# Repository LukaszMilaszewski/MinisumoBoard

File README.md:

# MinisumoBoard
electric board for minisumo robot designed in KiCad

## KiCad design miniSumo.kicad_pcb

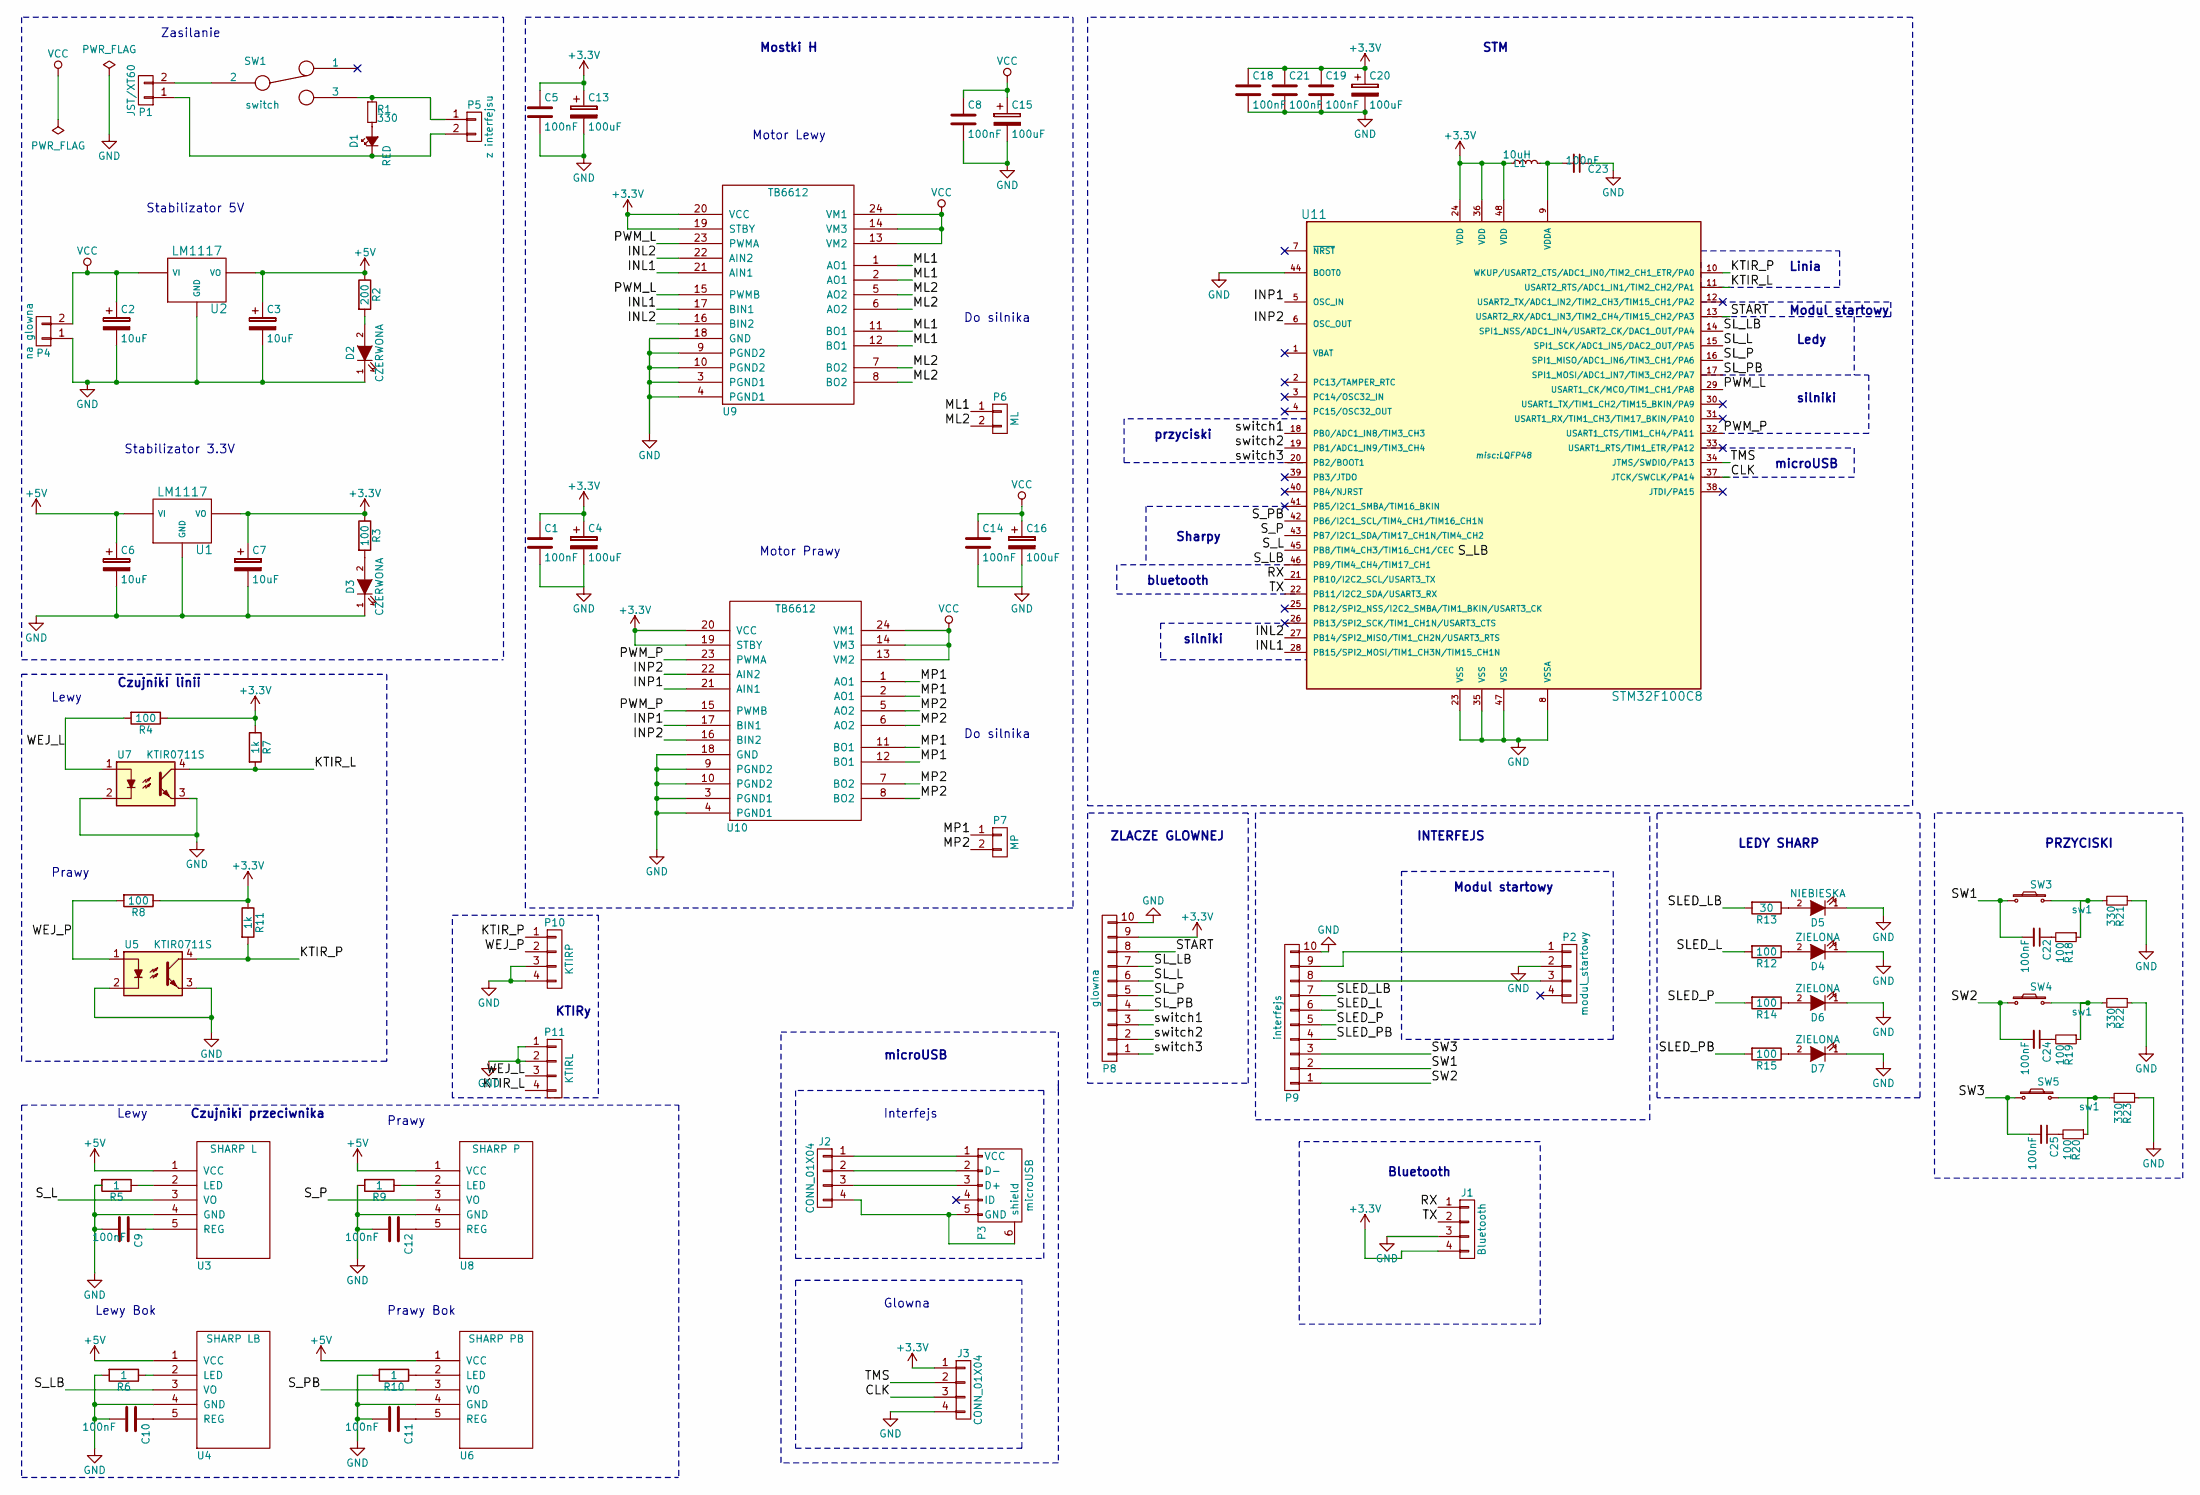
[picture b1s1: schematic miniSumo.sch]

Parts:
C1, C5, C8, C9, C10, C11, C12, C14, C18, C19, C21, C22, C23, C24, C25: 100nF; C_0805_HandSoldering
C2, C3, C6, C7: 10uF; CP_Tantalum_Case-B_EIA-3528-21_Hand
C4, C13, C15, C16, C20: 100uF; CP_Tantalum_Case-B_EIA-3528-21_Hand
D1: RED; LED_0805
D2, D3: CZERWONA; LED_0805
D4, D6, D7: ZIELONA; LED_0805
D5: NIEBIESKA; LED_0805
J1: Bluetooth; Pin_Header_Angled_1x04_Pitch2.00mm
J2: CONN_01X04; Pin_Header_Straight_1x04_Pitch2.00mm
J3: CONN_01X04; Pin_Header_Angled_1x04_Pitch2.00mm
L1: 10uH; R_0805
P1: JST/XT60; Pin_Header_Angled_1x02_Pitch2.00mm
P2: modul_startowy; Pin_Header_Straight_1x04_Pitch2.54mm
P3: microUSB; USB_Micro-B_10103594-0001LF
P4: na glowna; Pin_Header_Angled_1x02_Pitch2.00mm
P5: z interfejsu; Pin_Header_Angled_1x02_Pitch2.00mm
P6: ML; Pin_Header_Straight_1x02_Pitch2.54mm
P7: MP; Pin_Header_Straight_1x02_Pitch2.54mm
P8: glowna; Pin_Header_Angled_1x10_Pitch2.00mm
P9: interfejs; Pin_Header_Angled_1x10_Pitch2.00mm
P10: KTIRP; Pin_Header_Straight_1x04_Pitch2.54mm_SMD_Pin1Left
P11: KTIRL; Pin_Header_Straight_1x04_Pitch2.54mm_SMD_Pin1Right
R1, R21, R22, R23: 330; R_0805_HandSoldering
R2: 200; R_0805_HandSoldering
R3, R4, R8, R12, R14, R15, R18, R19, R20: 100; R_0805_HandSoldering
R5, R6, R9, R10: 1; R_0805_HandSoldering
R7, R11: 1k; R_0805_HandSoldering
R13: 30; R_0805_HandSoldering
SW1: switch; przelacznik_tht
SW3, SW4, SW5: sw1; tact_switch_smd
U1, U2: LM1117; LM1117_TO-220
U3: SHARP L; GP2Y0D340K_THC
U4: SHARP LB; GP2Y0D340K_THC
U5, U7: KTIR0711S
U6: SHARP PB; GP2Y0D340K_THC
U8: SHARP P; GP2Y0D340K_THC
U9, U10: TB6612
U11: STM32F100C8; LQFP48

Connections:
+3V3: C1.1, C4.1, C5.1, C7.1, C13.1, C18.1, C19.1, C20.1, C21.1, J1.4, J3.1, L1.1, P8.9, R3.1, R4.1, R7.1, R8.1, R11.1, U1.2 (VO), U9.19 (STBY), U9.20 (VCC), U10.19 (STBY), U10.20 (VCC), U11.24 (VDD), U11.36 (VDD), U11.48 (VDD)
+5V: C3.1, C6.1, R2.1, U1.1 (VI), U2.2 (VO), U3.1 (VCC), U4.1 (VCC), U6.1 (VCC), U8.1 (VCC)
/CLK: J3.3, U11.37 (JTCK/SWCLK/PA14)
/INL1: U9.17 (BIN1), U9.21 (AIN1), U11.28 (PB15/SPI2_MOSI/TIM1_CH3N/TIM15_CH1N)
/INL2: U9.16 (BIN2), U9.22 (AIN2), U11.27 (PB14/SPI2_MISO/TIM1_CH2N/USART3_RTS)
/INP1: U10.17 (BIN1), U10.21 (AIN1), U11.5 (OSC_IN)
/INP2: U10.16 (BIN2), U10.22 (AIN2), U11.6 (OSC_OUT)
/KTIR_L: P11.4, R7.2, U7.4, U11.11 (USART2_RTS/ADC1_IN1/TIM2_CH2/PA1)
/KTIR_P: P10.1, R11.2, U5.4, U11.10 (WKUP/USART2_CTS/ADC1_IN0/TIM2_CH1_ETR/P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)
/ML1: P6.1, U9.1 (AO1), U9.2 (AO1), U9.11 (BO1), U9.12 (BO1)
/ML2: P6.2, U9.5 (AO2), U9.6 (AO2), U9.7 (BO2), U9.8 (BO2)
/MP1: P7.1, U10.1 (AO1), U10.2 (AO1), U10.11 (BO1), U10.12 (BO1)
/MP2: P7.2, U10.5 (AO2), U10.6 (AO2), U10.7 (BO2), U10.8 (BO2)
/PWM_L: U9.15 (PWMB), U9.23 (PWMA), U11.29 (USART1_CK/MCO/TIM1_CH1/PA8)
/PWM_P: U10.15 (PWMB), U10.23 (PWMA), U11.32 (USART1_CTS/TIM1_CH4/PA11)
/RX: J1.1, U11.21 (PB10/I2C2_SCL/USART3_TX)
/SLED_L: P9.6, R12.2
/SLED_LB: P9.7, R13.2
/SLED_P: P9.5, R14.2
/SLED_PB: P9.4, R15.2
/SL_L: P8.6, U11.15 (SPI1_SCK/ADC1_IN5/DAC2_OUT/PA5)
/SL_LB: P8.7, U11.14 (SPI1_NSS/ADC1_IN4/USART2_CK/DAC1_OUT/PA4)
/SL_P: P8.5, U11.16 (SPI1_MISO/ADC1_IN6/TIM3_CH1/PA6)
/SL_PB: P8.4, U11.17 (SPI1_MOSI/ADC1_IN7/TIM3_CH2/PA7)
/START: P8.8, U11.13 (USART2_RX/ADC1_IN3/TIM2_CH4/TIM15_CH2/P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)
/SW1: C22.2, P9.2, SW3.1
/SW2: C24.2, P9.1, SW4.1
/SW3: C25.2, P9.3, SW5.1
/S_L: U3.3 (VO), U11.45 (PB8/TIM4_CH3/TIM16_CH1/CEC)
/S_LB: U4.3 (VO), U11.46 (PB9/TIM4_CH4/TIM17_CH1)
/S_P: U8.3 (VO), U11.43 (PB7/I2C1_SDA/TIM17_CH1N/TIM4_CH2)
/S_PB: U6.3 (VO), U11.42 (PB6/I2C1_SCL/TIM4_CH1/TIM16_CH1N)
/TMS: J3.2, U11.34 (JTMS/SWDIO/PA13)
/TX: J1.2, U11.22 (PB11/I2C2_SDA/USART3_RX)
/WEJ_L: P11.3, R4.2, U7.1
/WEJ_P: P10.2, R8.2, U5.1
/switch1: P8.3, U11.18 (PB0/ADC1_IN8/TIM3_CH3)
/switch2: P8.2, U11.19 (PB1/ADC1_IN9/TIM3_CH4)
/switch3: P8.1, U11.20 (PB2/BOOT1)
GND: C1.2, C2.2, C3.2, C4.2, C5.2, C6.2, C7.2, C8.2, C9.2, C10.2, C11.2, C12.2, C13.2, C14.2, C15.2, C16.2, C18.2, C19.2, C20.2, C21.2, C23.1, D2.1 (K), D3.1 (K), D4.1 (K), D5.1 (K), D6.1 (K), D7.1 (K), J1.3, J3.4, P2.2, P4.1, P8.10, P9.10, P10.3, P10.4, P11.1, P11.2, R5.2, R6.2, R9.2, R10.2, R21.1, R22.1, R23.1, U1.3 (GND), U2.3 (GND), U3.4 (GND), U4.4 (GND), U5.2, U5.3, U6.4 (GND), U7.2, U7.3, U8.4 (GND), U9.3 (PGND1), U9.4 (PGND1), U9.9 (PGND2), U9.10 (PGND2), U9.18 (GND), U10.3 (PGND1), U10.4 (PGND1), U10.9 (PGND2), U10.10 (PGND2), U10.18 (GND), U11.8 (VSSA), U11.23 (VSS), U11.35 (VSS), U11.44 (BOOT0), U11.47 (VSS)
unnamed: C9.1, U3.5 (REG)
unnamed: C10.1, U4.5 (REG)
unnamed: C11.1, U6.5 (REG)
unnamed: C12.1, U8.5 (REG)
unnamed: C22.1, R18.2
unnamed: C23.2, L1.2, U11.9 (VDDA)
unnamed: C24.1, R19.2
unnamed: C25.1, R20.2
unnamed: D1.1 (K), P1.1, P5.2
unnamed: D1.2 (A), R1.2
unnamed: D2.2 (A), R2.2
unnamed: D3.2 (A), R3.2
unnamed: D4.2 (A), R12.1
unnamed: D5.2 (A), R13.1
unnamed: D6.2 (A), R14.1
unnamed: D7.2 (A), R15.1
unnamed: J2.1, P3.1 (VCC)
unnamed: J2.2, P3.2 (D-)
unnamed: J2.3, P3.3 (D+)
unnamed: J2.4, P3.5 (GND), P3.6 (shield)
unnamed: P1.2, SW1.2
unnamed: P2.1, P9.9
unnamed: P2.3, P9.8
unnamed: P5.1, R1.1, SW1.3
unnamed: R5.1, U3.2 (LED)
unnamed: R6.1, U4.2 (LED)
unnamed: R9.1, U8.2 (LED)
unnamed: R10.1, U6.2 (LED)
unnamed: R18.1, R21.2, SW3.2
unnamed: R19.1, R22.2, SW4.2
unnamed: R20.1, R23.2, SW5.2
VCC: C2.1, C8.1, C14.1, C15.1, C16.1, P4.2, U2.1 (VI), U9.13 (VM2), U9.14 (VM3), U9.24 (VM1), U10.13 (VM2), U10.14 (VM3), U10.24 (VM1)

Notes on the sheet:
Stabilizator 5V
Zasilanie
Stabilizator 3.3V
Lewy Bok
Lewy
Prawy
Prawy Bok
Czujniki przeciwnika
Czujniki linii
Motor Lewy
Motor Prawy
Linia
STM
Do silnika
Mostki H
Modul startowy
INTERFEJS
ZLACZE GLOWNEJ
LEDY SHARP
PRZYCISKI
microUSB
Bluetooth
silniki
bluetooth
Sharpy
przyciski
Ledy
KTIRy
Interfejs
Glowna

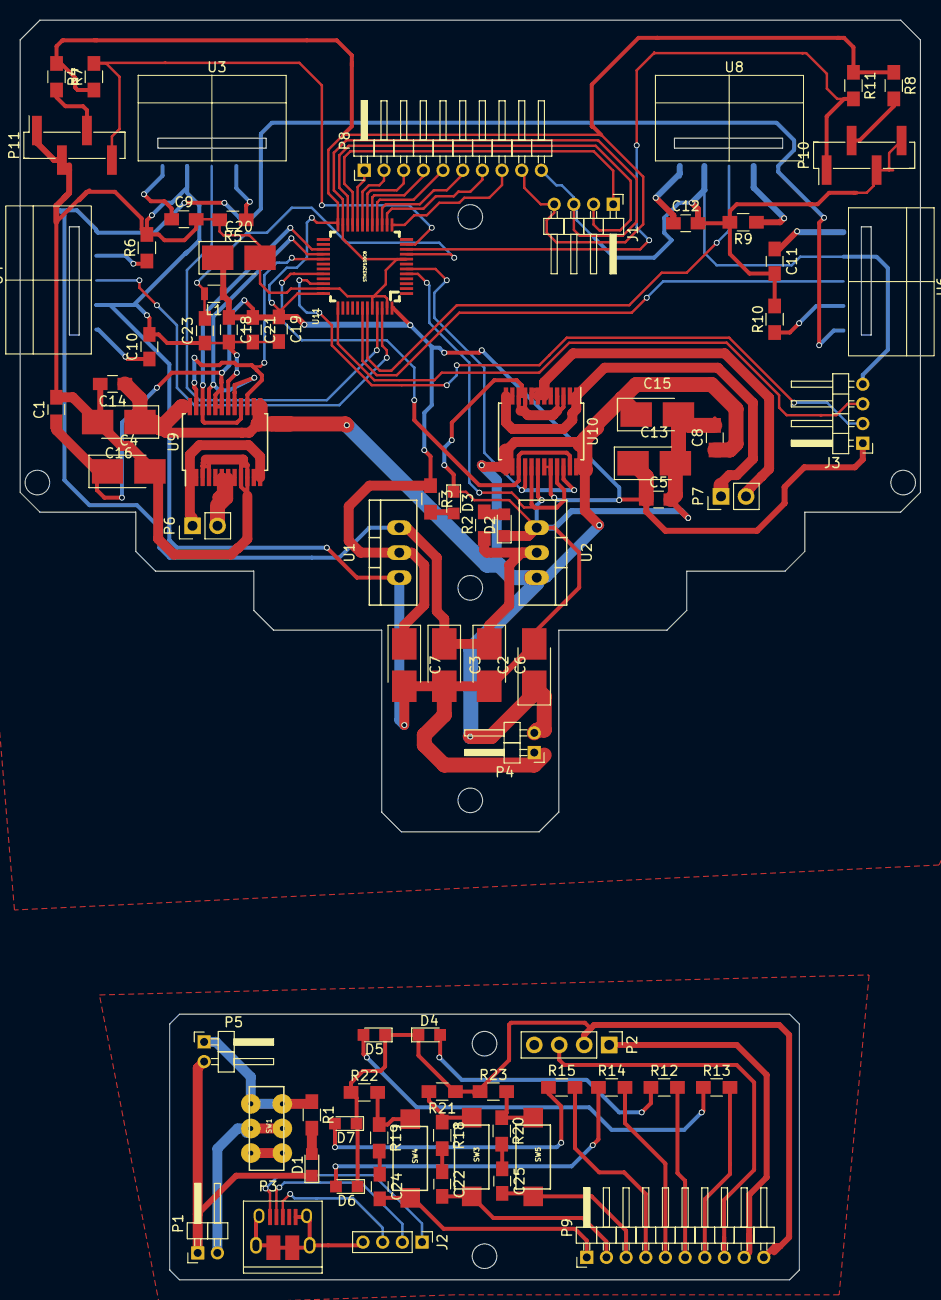
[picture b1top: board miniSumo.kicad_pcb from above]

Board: 2 copper layers, 91.5 x 128.0 mm, 80 parts (0 on the bottom side), 72 nets.

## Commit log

2017-09-16 added current electronic scheme
